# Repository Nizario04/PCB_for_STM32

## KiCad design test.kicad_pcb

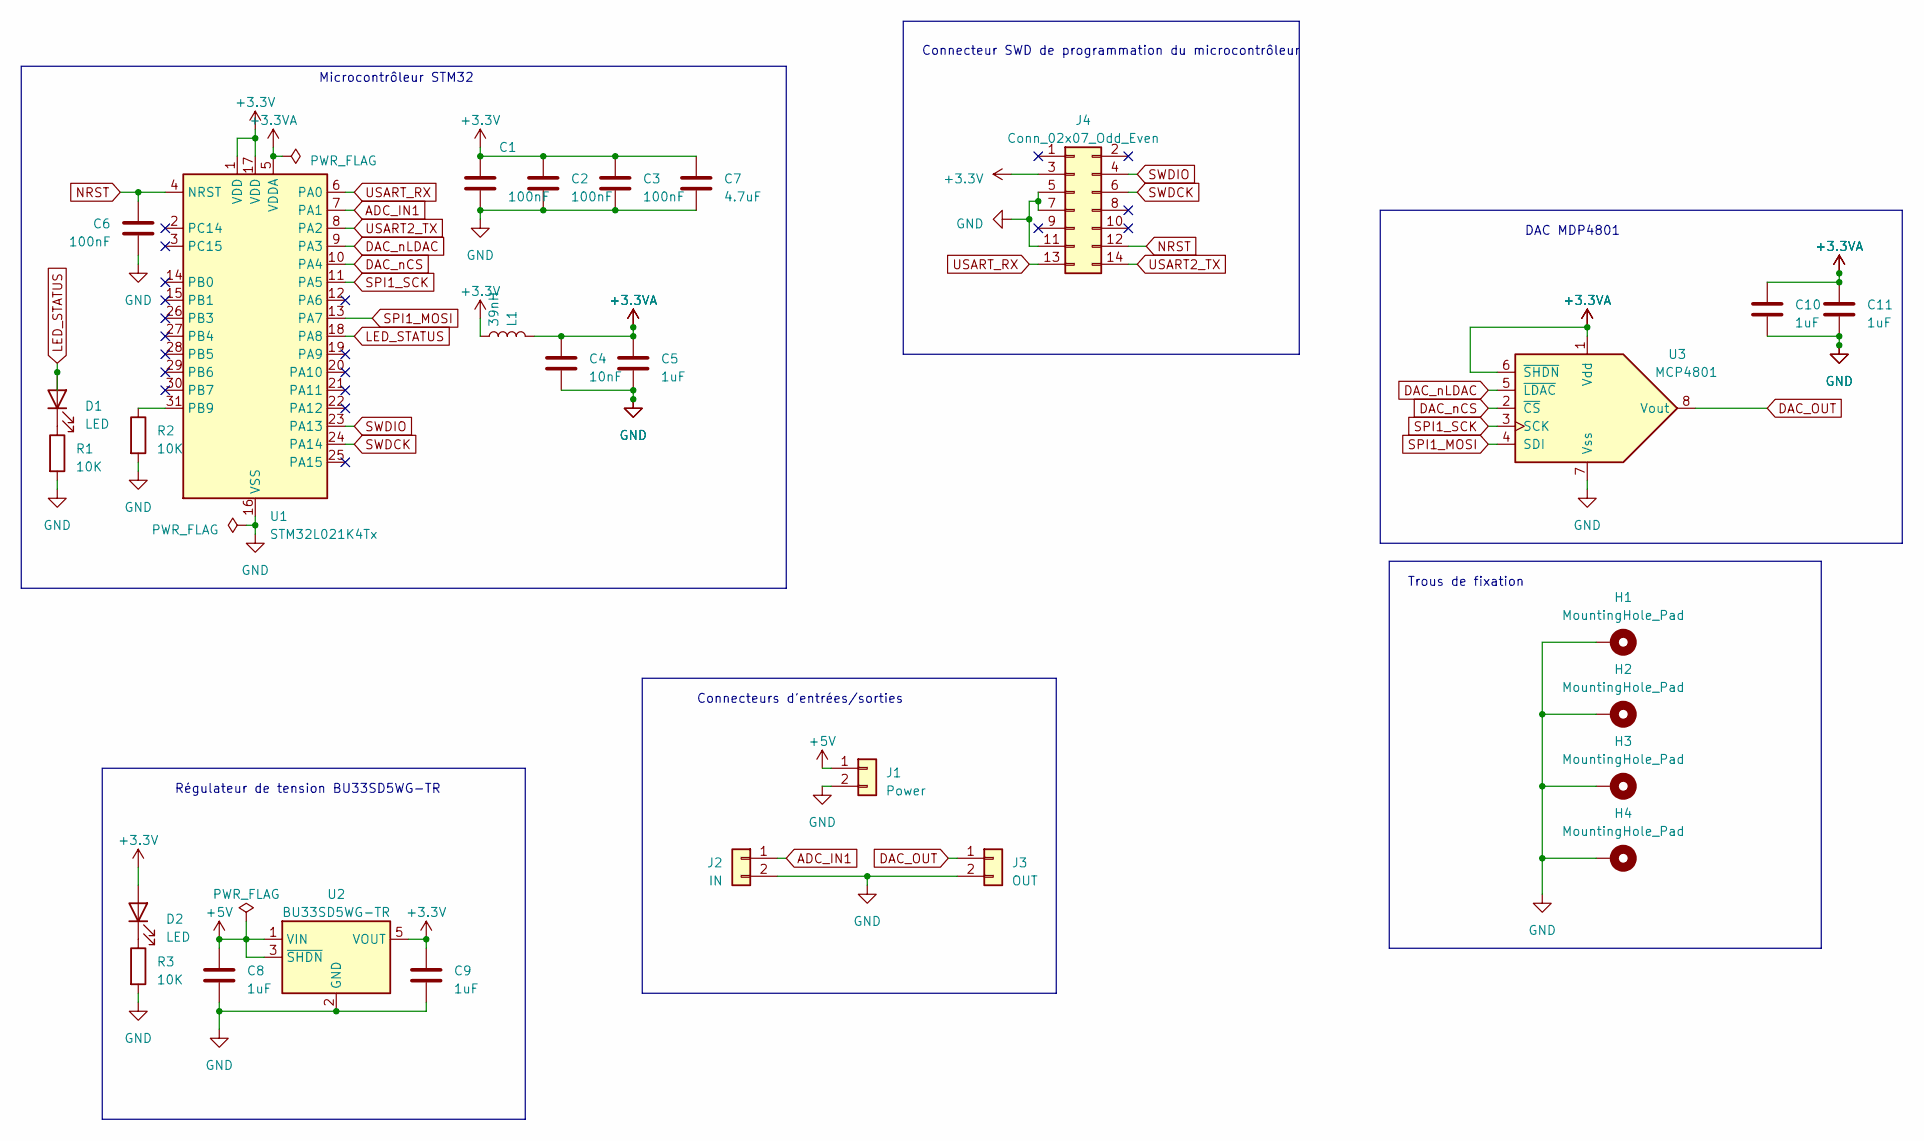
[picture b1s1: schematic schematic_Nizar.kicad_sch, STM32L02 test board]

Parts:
C1: 100nF
C2, C3, C6: 100nF; C_0603_1608Metric_Pad1.08x0.95mm_HandSolder
C4: 10nF; C_0603_1608Metric_Pad1.08x0.95mm_HandSolder
C5, C8, C9, C10, C11: 1uF; C_0603_1608Metric_Pad1.08x0.95mm_HandSolder
C7: 4.7uF; C_0603_1608Metric_Pad1.08x0.95mm_HandSolder
D1, D2: LED; LED_0603_1608Metric
H1, H2, H3, H4: MountingHole_Pad; MountingHole_3.2mm_M3_DIN965_Pad
J1: Power; JST_XH_B2B-XH-A_1x02_P2.50mm_Vertical
J2: IN; JST_XH_B2B-XH-A_1x02_P2.50mm_Vertical
J3: OUT; JST_XH_B2B-XH-A_1x02_P2.50mm_Vertical
J4: Conn_02x07_Odd_Even; PinHeader_2x07_P1.27mm_Vertical_SMD
L1: 39nH; L_0805_2012Metric_Pad1.05x1.20mm_HandSolder
R1, R2, R3: 10K; R_0603_1608Metric_Pad0.98x0.95mm_HandSolder
U1: STM32L021K4Tx; LQFP-32_7x7mm_P0.8mm
U2: BU33SD5WG-TR; SOT-23-5
U3: MCP4801; SOIC-8-1EP_3.9x4.9mm_P1.27mm_EP2.95x4.9mm_Mask2.71x3.4mm_Th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

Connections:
+3.3V: C1.1, C2.1, C3.1, C7.1, C9.1, D2.2 (A), J4.3, L1.2, U1.1 (VDD), U1.17 (VDD), U2.5 (VOUT)
+3.3VA: C4.1, C5.1, C10.1, C11.1, L1.1, U1.5 (VDDA), U3.1 (Vdd), U3.6 (~SHDN)
+5V: C8.1, J1.1, U2.1 (VIN), U2.3 (~SHDN)
ADC_IN1: J2.1, U1.7 (PA1)
DAC_OUT: J3.1, U3.8 (Vout)
DAC_nCS: U1.10 (PA4), U3.2 (~CS)
DAC_nLDAC: U1.9 (PA3), U3.5 (~LDAC)
GND: C1.2, C2.2, C3.2, C4.2, C5.2, C6.2, C7.2, C8.2, C9.2, C10.2, C11.2, H1.1, H2.1, H3.1, H4.1, J1.2, J2.2, J3.2, J4.5, J4.7, J4.11, R1.2, R2.2, R3.2, U1.16 (VSS), U1.32 (VSS), U2.2 (GND), U3.7 (Vss)
LED_STATUS: D1.2 (A), U1.18 (PA8)
NRST: C6.1, J4.12, U1.4 (NRST)
unnamed: D1.1 (K), R1.1
unnamed: D2.1 (K), R3.1
unnamed: R2.1, U1.31 (PB9)
SPI1_MOSI: U1.13 (PA7), U3.4 (SDI)
SPI1_SCK: U1.11 (PA5), U3.3 (SCK)
SWDCK: J4.6, U1.24 (PA14)
SWDIO: J4.4, U1.23 (PA13)
USART2_TX: J4.14, U1.8 (PA2)
USART_RX: J4.13, U1.6 (PA0)

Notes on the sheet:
Microcontrôleur STM32
DAC MDP4801
Connecteurs d'entrées/sorties
Régulateur de tension BU33SD5WG-TR
Trous de fixation
Connecteur SWD de programmation du microcontrôleur

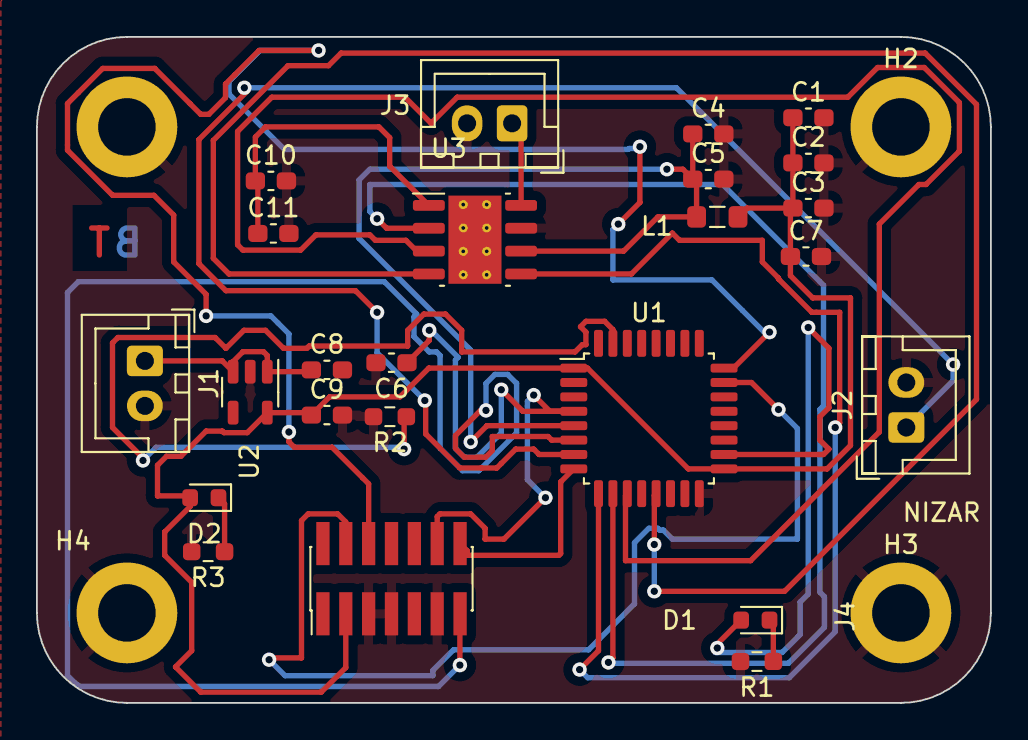
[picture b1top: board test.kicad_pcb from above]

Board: 2 copper layers, 53.0 x 37.0 mm, 28 parts (0 on the bottom side), 19 nets.
